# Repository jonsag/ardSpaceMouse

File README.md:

# ardSpaceMouse

An attempt to make a "mouse".  

Perhaps suited for CAD-work.  

A joystick to pan/zoom.  
Also a rotary encoder and three buttons for other purposes.  

!! Work in progress !!  

## Part list

* 1 x [Arduino Micro](https://www.amazon.se/DANDANdianzi-Leonardo-AT32U4-styrkort-ers%C3%A4ttning/dp/B086ZQK2FQ)
* 1 x [Joystick module](https://www.electrokit.com/produkt/analog-joystick-2-axel/)
* 1 x [Rotary encoder](https://www.electrokit.com/produkt/rotationsenkoder-24-p-v-med-tryckknapp/)
* 6 x [M2.5 screw](https://www.electrokit.com/produkt/skruv-ph-m2-5x6/)
* 4 x [1.6mm screw](https://www.electrokit.com/produkt/skruv-ph-m1-6x5/)
* 3 x [Micro switch](https://www.electrokit.com/produkt/tryckknapp-pcb-6x6x4-8mm-svart/)
* 6 x [M2.5 threaded insert](https://www.amazon.se/Symbiamo-Inserts-Threaded-Embedment-Assortment/dp/B09LM127D4)

## Links

[Space Mouse With Arduino Micro](https://www.instructables.com/Space-Mouse-With-Arduino-Micro-Fully-Printable/)  

[Creative Console for Space Mouse](https://www.instructables.com/Creative-Console-for-Space-Mouse/)  

[Keyboard Modifiers reference](https://www.arduino.cc/reference/en/language/functions/usb/keyboard/keyboardmodifiers/)  

[Another project on GitHub](https://github.com/soemarko/DIY-Space-Mouse)  

[Orbion 3D Space Mouse@github](https://github.com/FaqT0tum/Orbion_3D_Space_Mouse)  
[Orbion 3D Space Mouse@discord](https://discord.com/channels/920223684638179348/939922673646043176)

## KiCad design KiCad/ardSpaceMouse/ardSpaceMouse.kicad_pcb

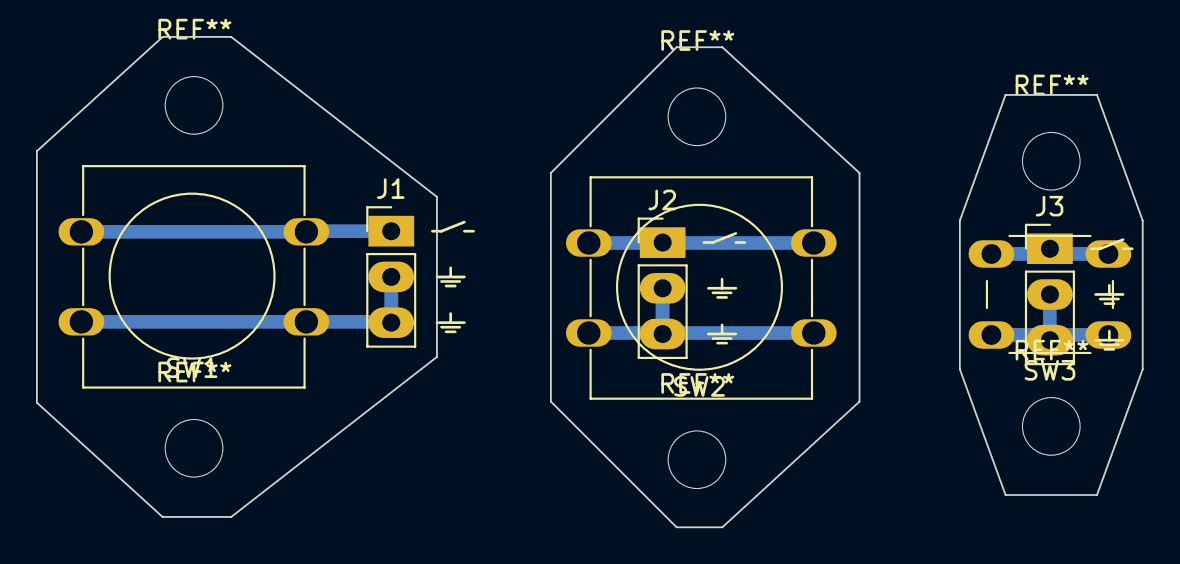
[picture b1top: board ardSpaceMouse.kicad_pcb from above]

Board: 2 copper layers, 61.4 x 27.2 mm, 6 parts (0 on the bottom side), 4 nets.

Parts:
J1, J2, J3: 3-pin_button+2xGND_header; 3-pin_button+2xGND_header_large
SW1, SW2: SW_Push; SW_PUSH-12mm_large
SW3: SW_Push; SW_PUSH_6mm_large

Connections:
GND: J1.2 (GND1), J1.3 (GND2), J2.2 (GND1), J2.3 (GND2), J3.2 (GND1), J3.3 (GND2), SW1.1, SW2.1, SW3.1
unnamed: J1.1 (Out), SW1.2
unnamed: J2.1 (Out), SW2.2
unnamed: J3.1 (Out), SW3.2

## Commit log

2022-01-10 Fix links
2022-01-10 Links
2022-01-10 more boards
2022-01-11 KiCAD
2022-01-15 scad
2022-01-22 scad updates
2022-01-22 readme
2022-01-30 OrbioSpaceMouse
2022-01-30 Orbion
2022-01-30 renames
2022-02-09 Orbion KiCAD
2022-02-09 added joystick
2022-04-28 mosgtly deletions
2022-04-28 orbion schematics
2022-05-12 orbion sources
2025-02-04 renamed orbion firmware directory
2025-02-04 workspace settings
